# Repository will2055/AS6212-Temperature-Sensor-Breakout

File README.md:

# AS6212-Temperature-Sensor-Breakout
Hardware repository for the AMS AS6212 Temperature Sensor

### AMS AS6212 Temperature Sensor

The highest performing AS6212 has an accuracy of +/- 0.2°C from -10°C to 65 °C. It provides a resolution of 16 bit over the wide temperature range from -40°C to 125°C. The integrated alarm functionality enables micro-controller wake-up calls on defined temperature thresholds. An internal voltage regulator allows stable accuracy independent of the supply voltage between 1.71V to 3.6V. For power sensitive applications, the device can enter a low-power wait mode with 0.1μA current consumption.

Documentation
--------------
* **[Main Repository](https://github.com/will2055/AS6212-Temperature-Sensor-Breakout)** - Main repository (including hardware files) for the temperature sensor.
* **[Arduino Library](https://github.com/will2055/AS6212-Arduino-Library)** - Repository containing the Arduino library software to interface with this sensor.

License Information
-------------------

This project is _**open source**_! 

Please review the LICENSE.md file for license information
Distributed as-is; no warranty is given.

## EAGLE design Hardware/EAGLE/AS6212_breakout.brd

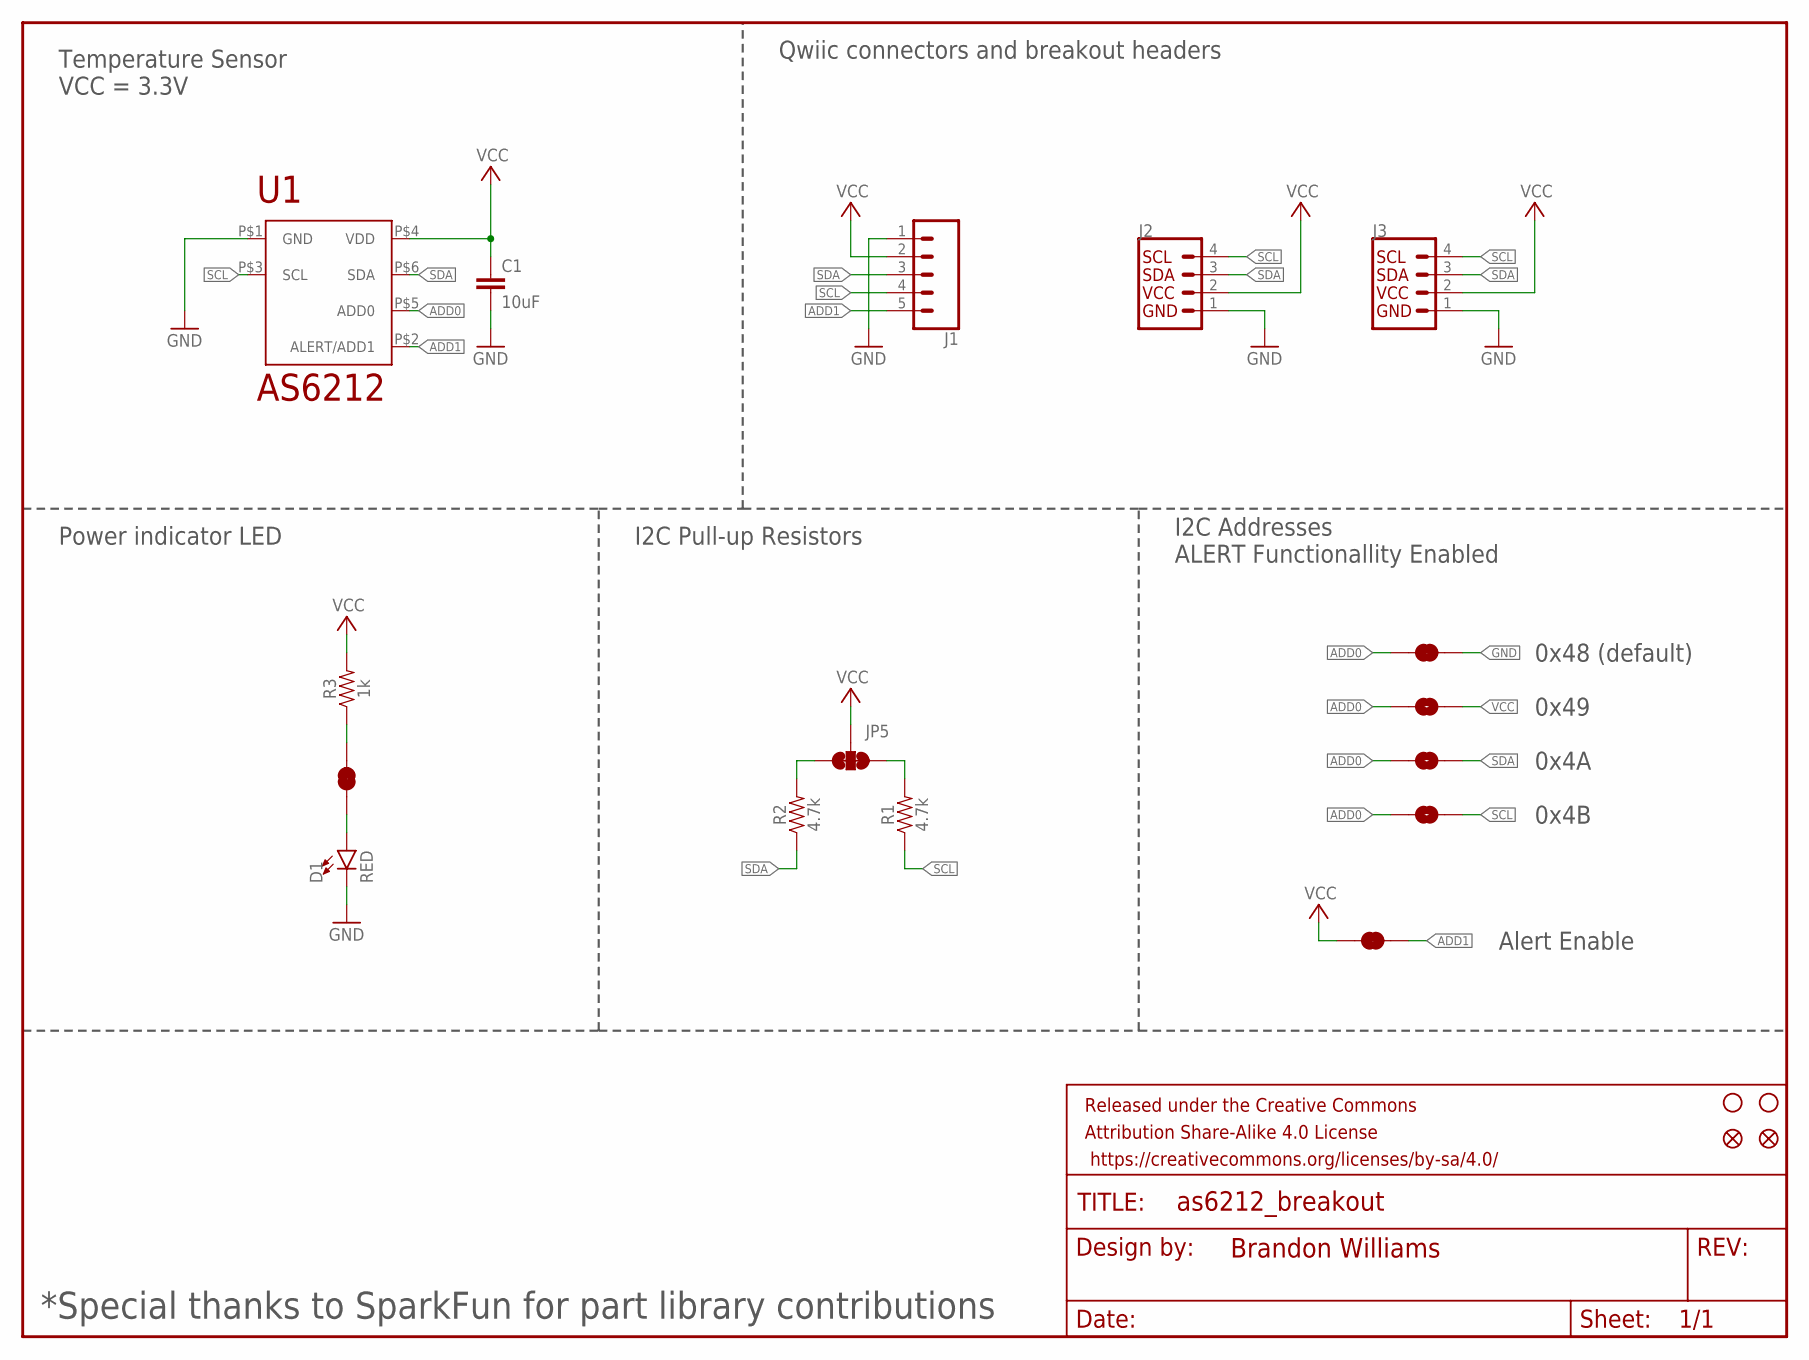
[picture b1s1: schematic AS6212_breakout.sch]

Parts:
C1: 10uF; 0805
D1: RED; LED-0603
FD1, FD2: FIDUCIAL0.2MM; FIDUCIAL-0.2MM
FRAME1: FRAME-LETTERNO_PACKAGE; DUMMY
H1, H2: STAND-OFF
J1: CONN_05; 1X05
J2, J3: QWIIC_RIGHT_ANGLE; JST04_1MM_RA
JP1, JP2, JP3: JUMPER-SMT_2_NO_SILK; SMT-JUMPER_2_NO_SILK
JP4, JP6, JP7: JUMPER-SMT_2_NC_TRACE_SILK; SMT-JUMPER_2_NC_TRACE_SILK
JP5: JUMPER-SMT_3_2-NC_TRACE_SILK; SMT-JUMPER_3_2-NC_TRACE_SILK
R1, R2: 4.7k; 0603
R3: 1k; 0603
U1: AS6212

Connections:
ADD0: JP1.1, JP2.1, JP3.1, JP4.1, U1.P$5 (ADD0)
ADD1: J1.5, JP6.2, U1.P$2 (ALERT/ADD1)
GND: C1.2, D1.C, J1.1, J2.1, J3.1, JP4.2, U1.P$1 (GND)
unnamed: JP5.3, R2.2
unnamed: JP5.1, R1.2
unnamed: JP7.2, R3.1
unnamed: D1.A, JP7.1
SCL: J1.4, J2.4, J3.4, JP2.2, R1.1, U1.P$3 (SCL)
SDA: J1.3, J2.3, J3.3, JP1.2, R2.1, U1.P$6 (SDA)
VCC: C1.1, J1.2, J2.2, J3.2, JP3.2, JP5.2, JP6.1, R3.2, U1.P$4 (VDD)

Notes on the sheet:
Temperature Sensor VCC = 3.3V
Qwiic connectors and breakout headers
Power indicator LED
I2C Pull-up Resistors
I2C Addresses ALERT Functionallity Enabled
0x48 (default)
0x49
0x4A
0x4B
Alert Enable
*Special thanks to SparkFun for part library contributions

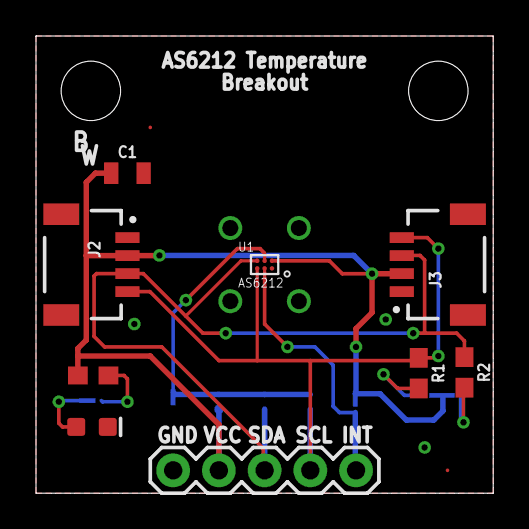
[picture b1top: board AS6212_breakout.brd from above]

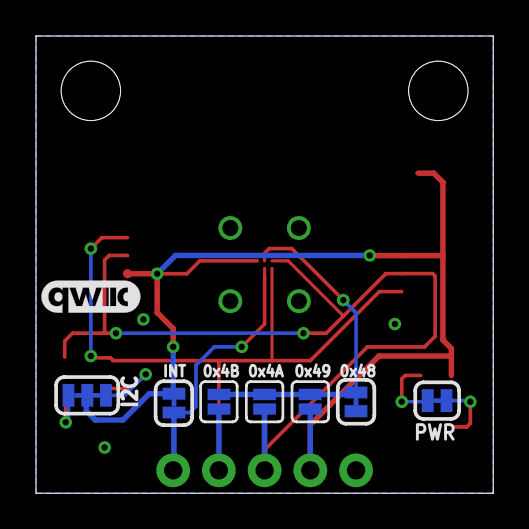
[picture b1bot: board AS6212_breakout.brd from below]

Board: 2 copper layers, 25.4 x 25.4 mm, 22 parts (8 on the bottom side), 10 nets.

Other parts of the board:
U$1: QWIIC_5.5MM

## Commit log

2020-06-16 Add EAGLE files via upload
2020-06-17 Verify Github Upload
2020-06-17 Adding software src library files v0.1
2020-06-17 minor schematic changes to EAGLE files
2020-06-17 remove incorrect files
2020-06-24 fixed pin layout issue
    pins were swapped, moved to right locations
2020-06-26 Board Layout Revision
    Changing board features for new footprint library
2020-07-22 v01 main push
    Updated Eagle files and source software
2020-07-29 Rev 02 push
    First production version of breakout board - push ready
2020-07-29 Clean up Software Directory
    Upload small updates to source files and clean up directory
2020-07-29 v1.01 Source Update
    Added threshold functions and configuration register functions.
2020-07-31 Configuration register updates
    small changes to software and hardware.
2020-08-14 JLCPCB Tolerances
    updates design rules for minimum JLCPCB specs
2020-08-30 Clutter Clean-up
    Clean-up before first version release
2020-08-30 Clean-up
2020-08-30 Clean-up for release 0.5
2020-09-01 Remove Experimental Folder
    Removing experimental master branch. Using experimental.01 to test issues.
2020-09-16 Bug fixes
    Added thank you in schematic as well
2020-10-07 Update README.md
    Preparation to split library into hardware and software
2021-06-17 Board design rework & datasheet upload

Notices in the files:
parts and their libraries:
SparkFun-Capacitors: Licensing: Creative Commons ShareAlike 4.0 International - https://creativecommons.org/licenses/by-sa/4.0
SparkFun-Aesthetics: Released under the Creative Commons Attribution Share-Alike 4.0 License
SparkFun-Aesthetics: https://creativecommons.org/licenses/by-sa/4.0
